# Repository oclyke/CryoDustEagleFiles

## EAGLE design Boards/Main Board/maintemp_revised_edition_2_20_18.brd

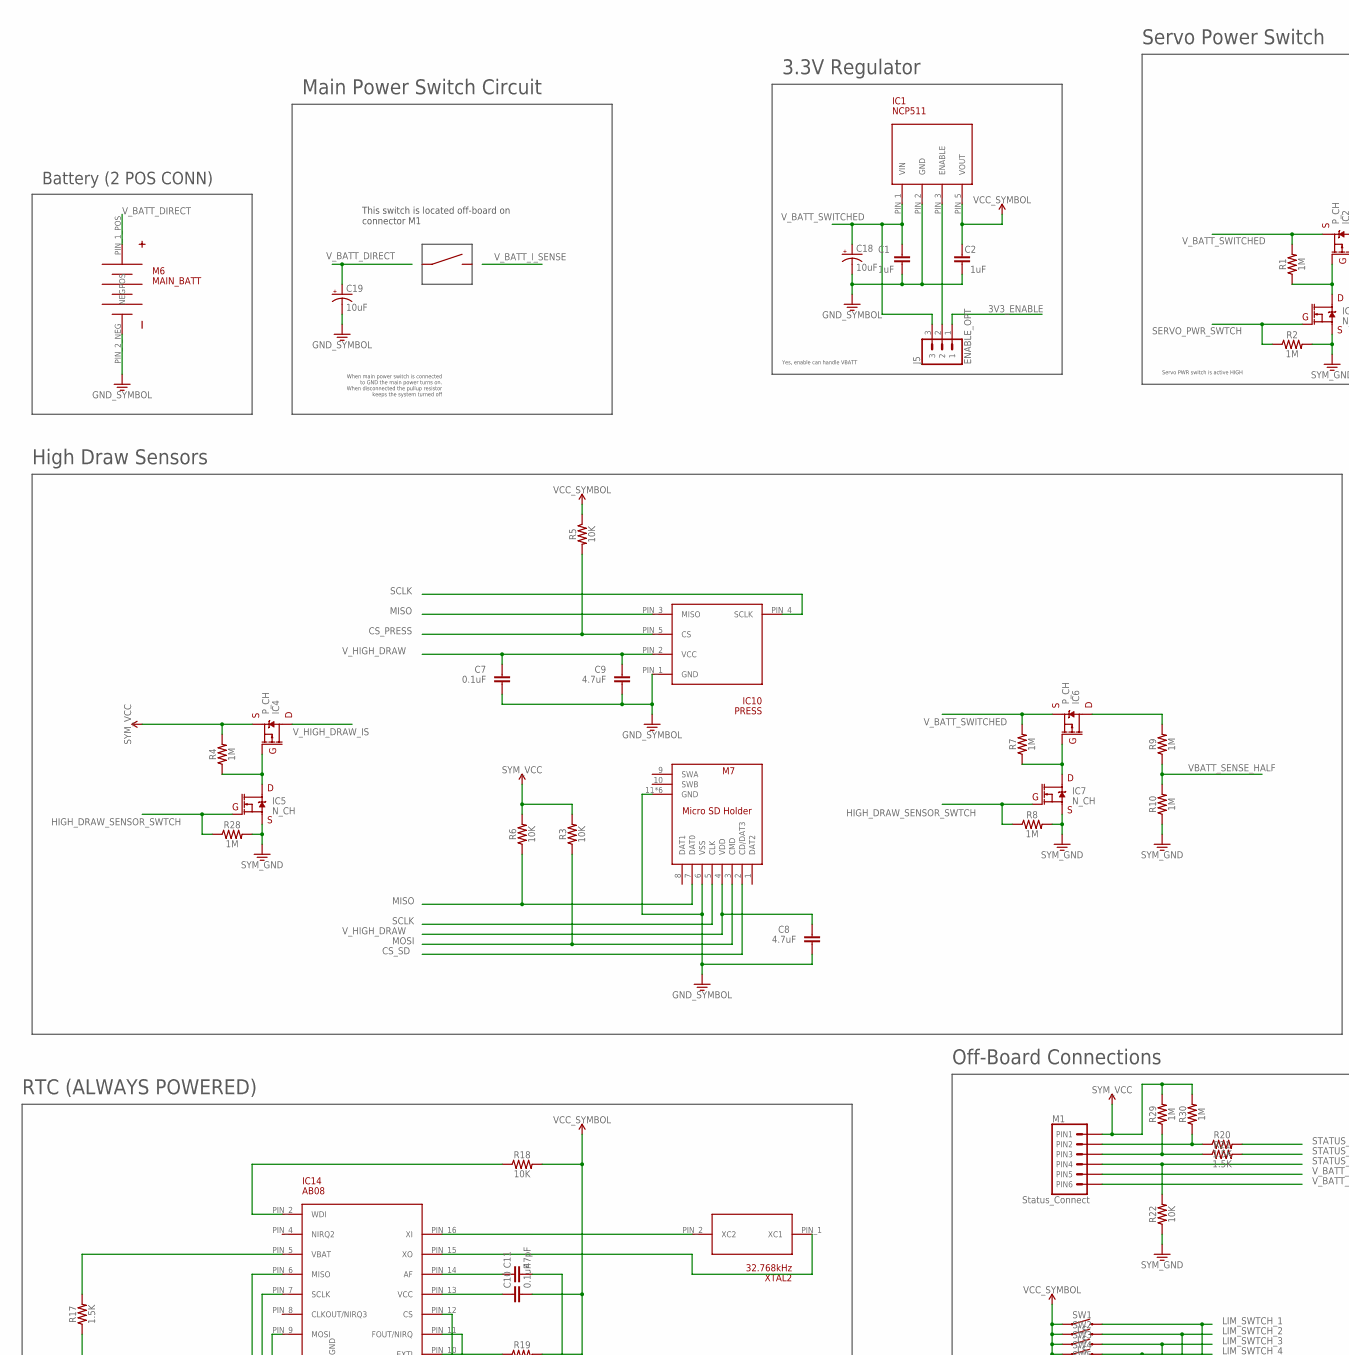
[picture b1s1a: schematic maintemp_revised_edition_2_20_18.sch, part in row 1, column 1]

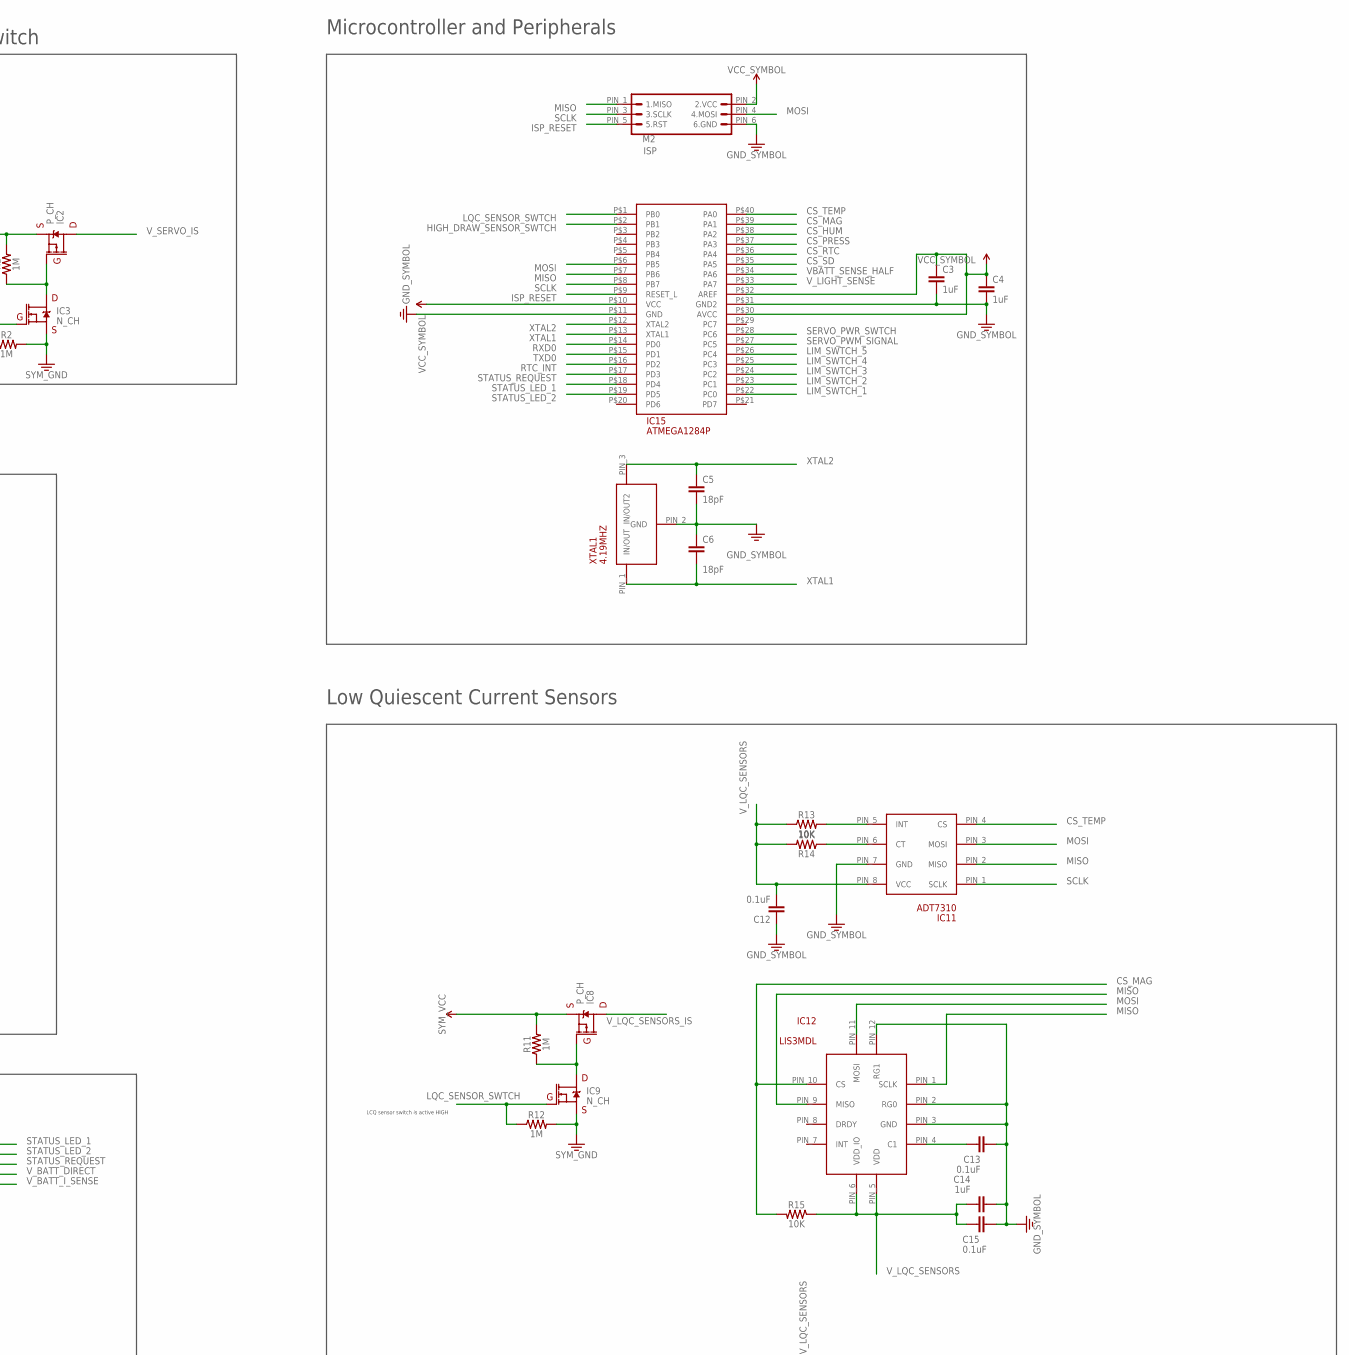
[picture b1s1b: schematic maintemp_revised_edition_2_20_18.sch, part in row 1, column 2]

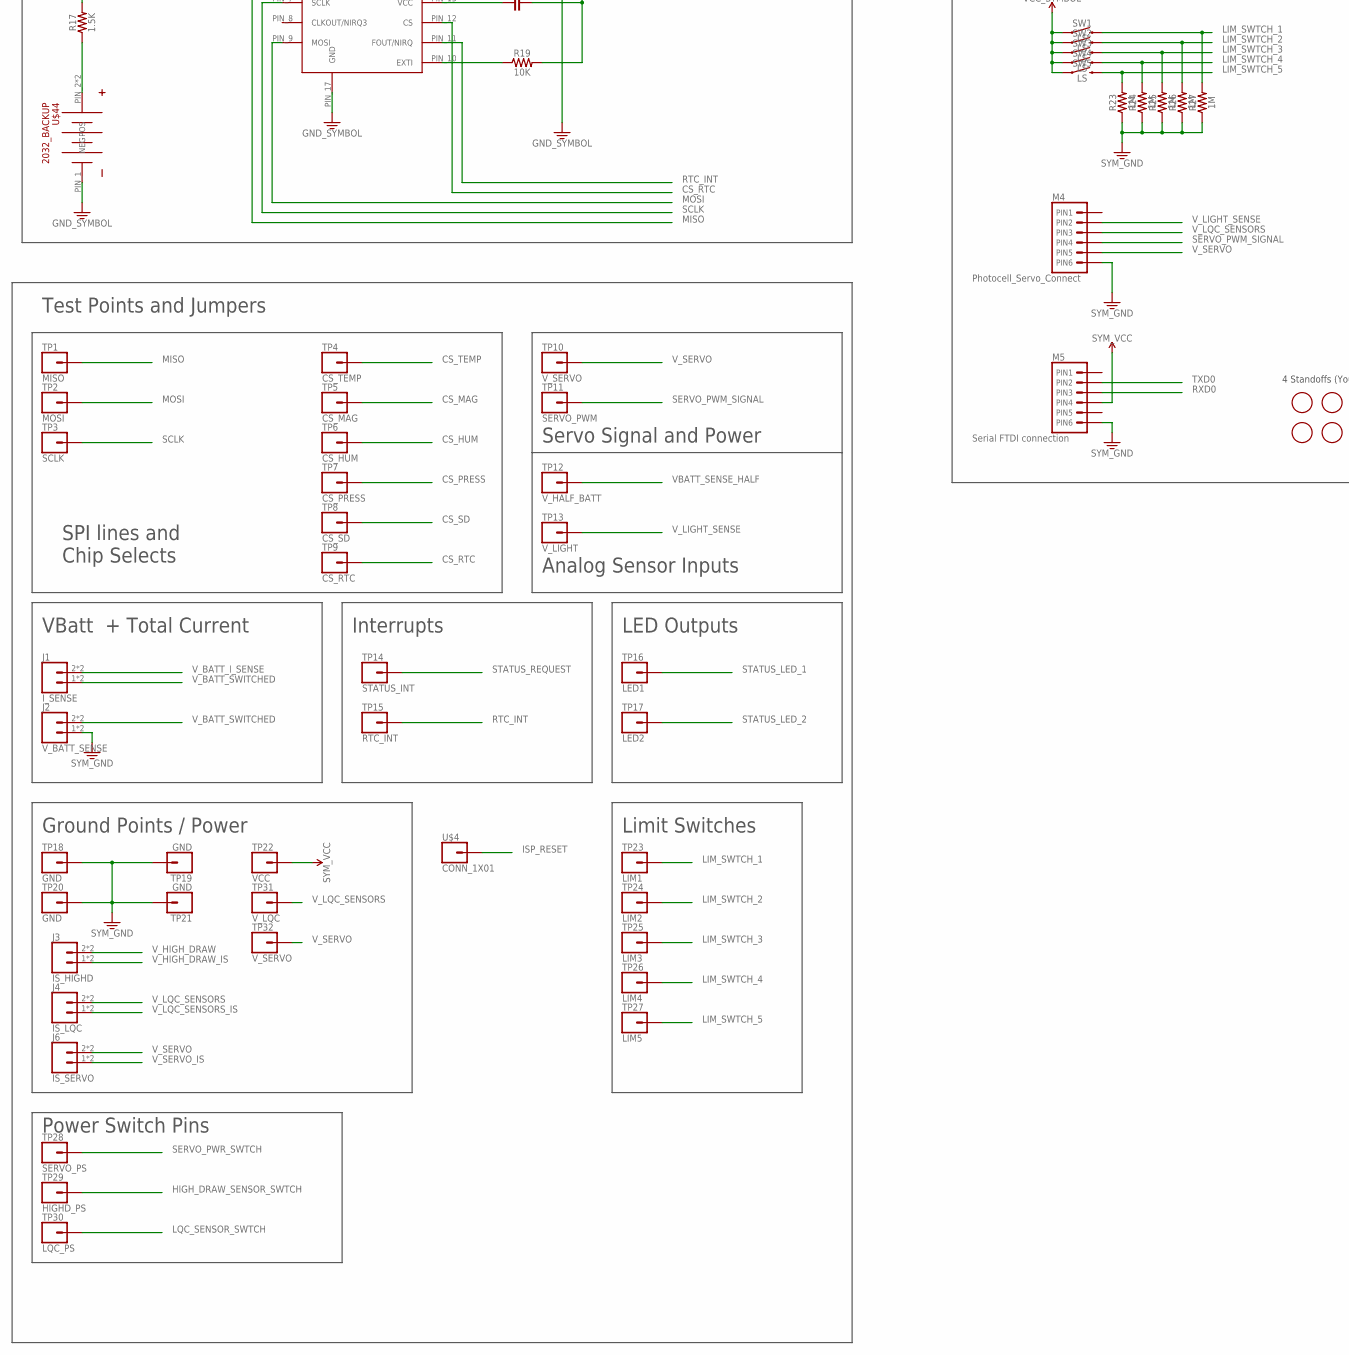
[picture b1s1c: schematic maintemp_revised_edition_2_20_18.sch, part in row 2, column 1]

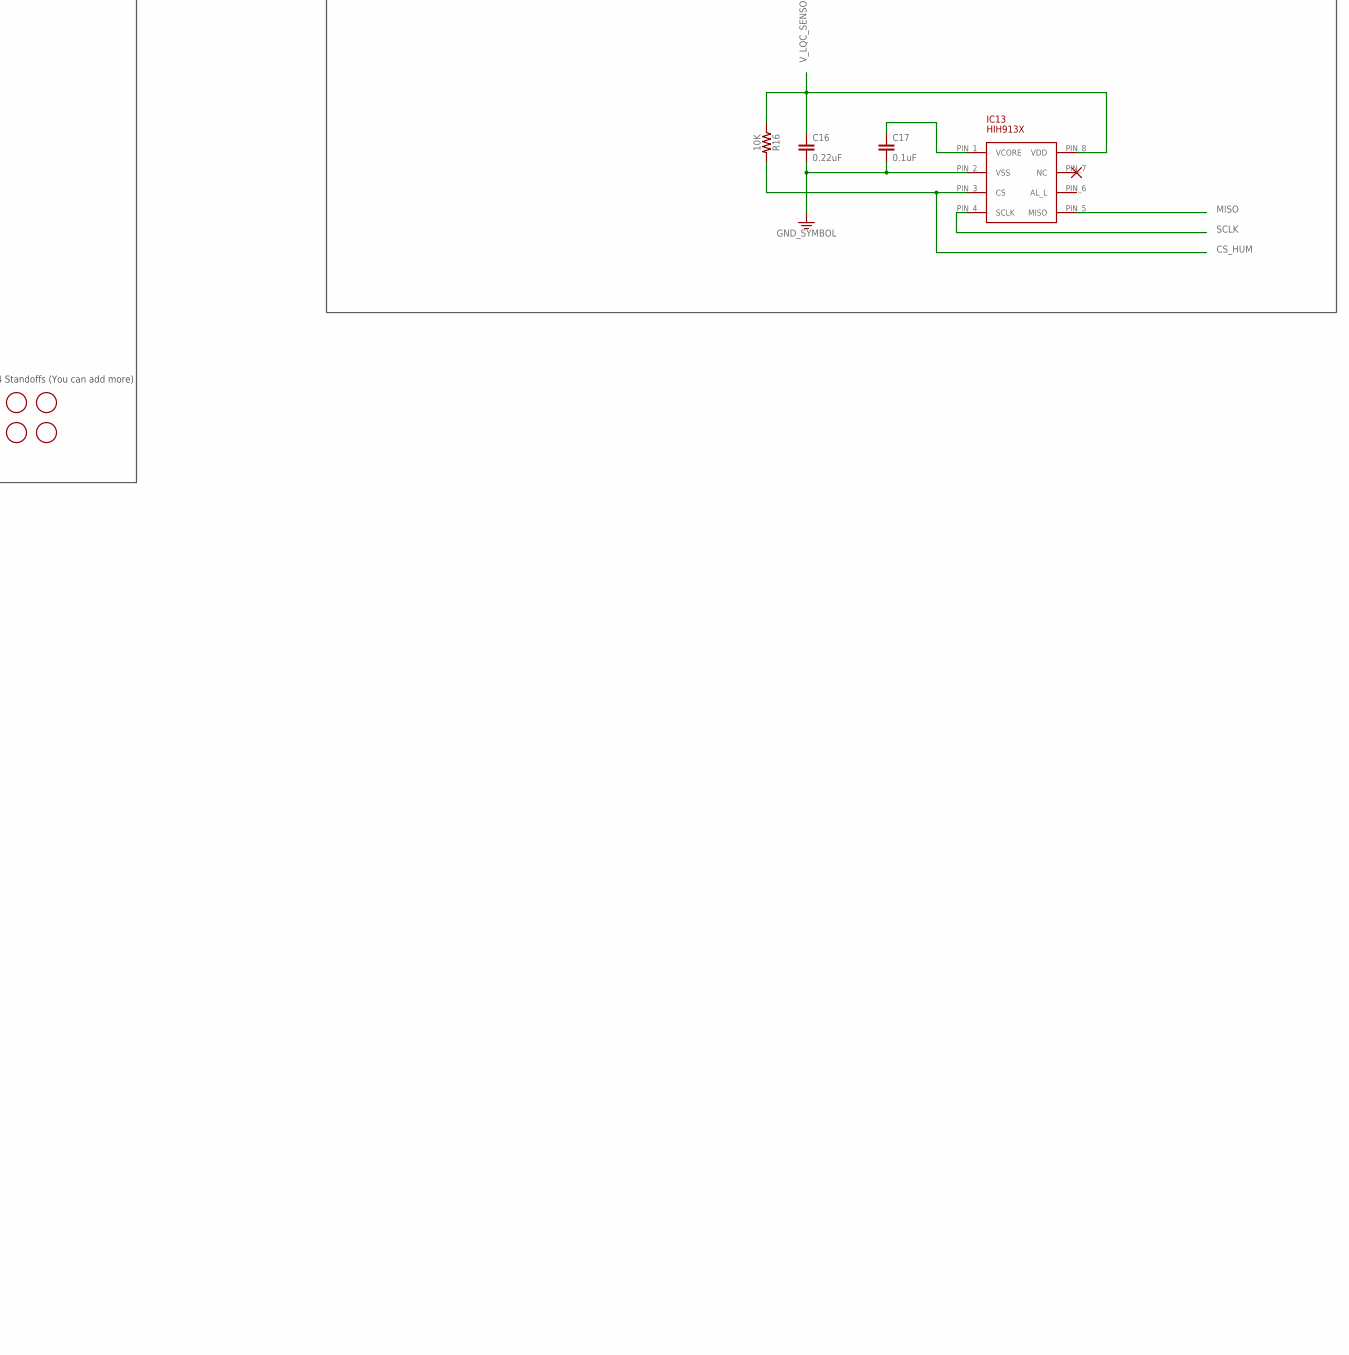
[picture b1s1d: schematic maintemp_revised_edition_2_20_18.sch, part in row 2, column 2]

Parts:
C1, C2, C3, C4, C14: 1uF; SMD_0603
C5, C6: 18pF; SMD_0603
C7, C12, C13, C15, C17: 0.1uF; SMD_0603
C8, C9: 4.7uF; SMD_0603
C10: 0.1uF; 0603
C11: 47pF; 0603
C16: 0.22uF; SMD_0603
C18, C19: 10uF; CAP-PTH-2.54
IC1: NCP511; TSOP-5
IC2, IC4, IC6, IC8: P_CH; SOT23
IC3, IC5, IC7, IC9: N_CH; SOT23
IC10: PRESS; 8-DIP
IC11: ADT7310; SOIC-8
IC12: LIS3MDL; LGA-12
IC13: HIH913X; SOIC-8
IC14: AB08; QFN16_3X3
IC15: ATMEGA1284P; 40-DIP
J1: I_SENSE; 1X02
J2: V_BATT_SENSE; 1X02
J3: IS_HIGHD; 1X02
J4: IS_LQC; 1X02
J5: ENABLE_OPT; 1X03
J6: IS_SERVO; 1X02
M1: Status_Connect; 1X06
M2: ISP; 2X3
M4: Photocell_Servo_Connect; 1X06
M5: Serial FTDI connection; 1X06
M6: MAIN_BATT; 1-1318300-2
M7: SD; MICRO-SD
R1, R2, R4, R7, R8, R9, R10, R11, R12, R23, R24, R25, R26, R27, R28, R29, R30: 1M; SMD_0603
R3, R5, R6, R13, R14, R15, R16, R22: 10K; SMD_0603
R17: 1.5K; 0603
R18, R19: 10K; 0603
R20, R21: 1.5K; SMD_0603
SW1, SW2, SW3, SW4, SW5: LS; SNAPSWITCH
TP1: MISO; 1X01
TP2: MOSI; 1X01
TP3: SCLK; 1X01
TP4: CS_TEMP; 1X01
TP5: CS_MAG; 1X01
TP6: CS_HUM; 1X01
TP7: CS_PRESS; 1X01
TP8: CS_SD; 1X01
TP9: CS_RTC; 1X01
TP10, TP32: V_SERVO; 1X01
TP11: SERVO_PWM; 1X01
TP12: V_HALF_BATT; 1X01
TP13: V_LIGHT; 1X01
TP14: STATUS_INT; 1X01
TP15: RTC_INT; 1X01
TP16: LED1; 1X01
TP17: LED2; 1X01
TP18, TP19, TP20, TP21: GND; 1X01
TP22: VCC; 1X01
TP23: LIM1; 1X01
TP24: LIM2; 1X01
TP25: LIM3; 1X01
TP26: LIM4; 1X01
TP27: LIM5; 1X01
TP28: SERVO_PS; 1X01
TP29: HIGHD_PS; 1X01
TP30: LQC_PS; 1X01
TP31: V_LQC; 1X01
U$4: CONN_1X01; 1X01
U$7, U$11, U$13, U$17: STANDOFF
U$44: 2032_BACKUP; 2032
XTAL1: 4.19MHZ; AT49
XTAL2: 32.768kHz; ABS07

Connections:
3V3_ENABLE: J5.1
CS_HUM: IC13.PIN_3 (CS), IC15.P$38 (PA2), R16.P$2 (2), TP6.1
CS_MAG: IC12.PIN_10 (CS), IC15.P$39 (PA1), R15.P$2 (2), TP5.1
CS_PRESS: IC10.PIN_5 (CS), IC15.P$37 (PA3), R5.P$2 (2), TP7.1
CS_RTC: IC14.PIN_12 (CS), IC15.P$36 (PA4), TP9.1
CS_SD: IC15.P$35 (PA5), M7.2 (CD/DAT3), TP8.1
CS_TEMP: IC11.PIN_4 (CS), IC15.P$40 (PA0), TP4.1
GND: C1.P$2 (2), C2.P$1 (1), C3.P$2 (2), C4.P$2 (2), C5.P$2 (2), C6.P$1 (1), C7.P$2 (2), C8.P$1 (1), C9.P$2 (2), C11.2, C12.P$1 (1), C13.P$1 (1), C14.P$1 (1), C15.P$2 (2), C16.P$2 (2), C17.P$2 (2), C18.2 (-), C19.2 (-), IC1.PIN_2 (GND), IC3.2 (S), IC5.2 (S), IC7.2 (S), IC9.2 (S), IC10.PIN_1 (GND), IC11.PIN_7 (GND), IC12.PIN_2 (RG0), IC12.PIN_3 (GND), IC12.PIN_12 (RG1), IC13.PIN_2 (VSS), IC14.PIN_17 (GND), IC15.P$11 (GND), IC15.P$31 (GND2), J2.1, J2.P$1 (1), M2.PIN_6 (6.GND), M4.1 (PIN6), M5.1 (PIN6), M6.PIN_2_NEG (NEG), M7.6 (VSS), M7.11 (GND), M7.12 (GND), M7.13 (GND), M7.14 (GND), M7.15 (GND), M7.16 (GND), R2.P$2 (2), R8.P$2 (2), R10.P$1 (1), R12.P$2 (2), R22.P$1 (1), R23.P$1 (1), R24.P$1 (1), R25.P$1 (1), R26.P$1 (1), R27.P$1 (1), R28.P$2 (2), TP18.1, TP19.1, TP20.1, TP21.1, U$44.PIN_1 (NEG), XTAL1.PIN_2 (GND)
HIGH_DRAW_SENSOR_SWTCH: IC5.1 (G), IC7.1 (G), IC15.P$2 (PB1), R8.P$1 (1), R28.P$1 (1), TP29.1
ISP_RESET: IC15.P$9 (RESET_L), M2.PIN_5 (5.RST), U$4.1
LIM_SWTCH_1: IC15.P$22 (PC0), R27.P$2 (2), SW1.PIN_2 (2), TP23.1
LIM_SWTCH_2: IC15.P$23 (PC1), R26.P$2 (2), SW2.PIN_2 (2), TP24.1
LIM_SWTCH_3: IC15.P$24 (PC2), R25.P$2 (2), SW3.PIN_2 (2), TP25.1
LIM_SWTCH_4: IC15.P$25 (PC3), R24.P$2 (2), SW4.PIN_2 (2), TP26.1
LIM_SWTCH_5: IC15.P$26 (PC4), R23.P$2 (2), SW5.PIN_2 (2), TP27.1
LQC_SENSOR_SWTCH: IC9.1 (G), IC15.P$1 (PB0), R12.P$1 (1), TP30.1
MISO: IC10.PIN_3 (MISO), IC11.PIN_2 (MISO), IC12.PIN_1 (SCLK), IC12.PIN_9 (MISO), IC13.PIN_5 (MISO), IC14.PIN_6 (MISO), IC15.P$7 (PB6), M2.PIN_1 (1.MISO), M7.7 (DAT0), R6.P$1 (1), TP1.1
MOSI: IC11.PIN_3 (MOSI), IC12.PIN_11 (MOSI), IC14.PIN_9 (MOSI), IC15.P$6 (PB5), M2.PIN_4 (4.MOSI), M7.3 (CMD), R3.P$1 (1), TP2.1
unnamed: IC2.1 (G), IC3.3 (D), R1.P$1 (1)
unnamed: C17.P$1 (1), IC13.PIN_1 (VCORE)
unnamed: C13.P$2 (2), IC12.PIN_4 (C1)
unnamed: IC14.PIN_2 (WDI), R18.1
unnamed: IC14.PIN_10 (EXTI), R19.1
unnamed: C10.1, IC14.PIN_13 (VCC)
unnamed: C11.1, IC14.PIN_14 (AF)
unnamed: IC14.PIN_15 (XO), XTAL2.PIN_1 (XC1)
unnamed: IC14.PIN_16 (XI), XTAL2.PIN_2 (XC2)
unnamed: R17.1, U$44.PIN_2 (POS), U$44.PIN_3 (POS)
unnamed: IC14.PIN_5 (VBAT), R17.2
unnamed: IC11.PIN_5 (INT), R13.P$2 (2)
unnamed: IC11.PIN_6 (CT), R14.P$1 (1)
unnamed: IC1.PIN_3 (ENABLE), J5.2
unnamed: IC6.1 (G), IC7.3 (D), R7.P$1 (1)
unnamed: IC4.1 (G), IC5.3 (D), R4.P$1 (1)
unnamed: IC8.1 (G), IC9.3 (D), R11.P$1 (1)
N$L1: M1.5 (PIN2), R20.P$1 (1), R30.P$1 (1)
N$L2: M1.4 (PIN3), R21.P$1 (1), R29.P$1 (1)
RTC_INT: IC14.PIN_11 (FOUT/NIRQ), IC15.P$16 (PD2), TP15.1
RXD0: IC15.P$14 (PD0), M5.4 (PIN3)
SCLK: IC10.PIN_4 (SCLK), IC11.PIN_1 (SCLK), IC13.PIN_4 (SCLK), IC14.PIN_7 (SCLK), IC15.P$8 (PB7), M2.PIN_3 (3.SCLK), M7.5 (CLK), TP3.1
SERVO_PWM_SIGNAL: IC15.P$27 (PC5), M4.3 (PIN4), TP11.1
SERVO_PWR_SWTCH: IC3.1 (G), IC15.P$28 (PC6), R2.P$1 (1), TP28.1
STATUS_LED_1: IC15.P$18 (PD4), R20.P$2 (2), TP16.1
STATUS_LED_2: IC15.P$19 (PD5), R21.P$2 (2), TP17.1
STATUS_REQUEST: IC15.P$17 (PD3), M1.3 (PIN4), R22.P$2 (2), TP14.1
TXD0: IC15.P$15 (PD1), M5.5 (PIN2)
VBATT_SENSE_HALF: IC15.P$34 (PA6), R9.P$1 (1), R10.P$2 (2), TP12.1
VCC: C2.P$2 (2), C3.P$1 (1), C4.P$1 (1), C10.2, IC1.PIN_5 (VOUT), IC4.2 (S), IC8.2 (S), IC15.P$10 (VCC), IC15.P$30 (AVCC), IC15.P$32 (AREF), M1.6 (PIN1), M2.PIN_2 (2.VCC), M5.3 (PIN4), R3.P$2 (2), R4.P$2 (2), R5.P$1 (1), R6.P$2 (2), R11.P$2 (2), R18.2, R19.2, R29.P$2 (2), R30.P$2 (2), SW1.PIN_1 (1), SW2.PIN_1 (1), SW3.PIN_1 (1), SW4.PIN_1 (1), SW5.PIN_1 (1), TP22.1
V_BATT_DIRECT: C19.1 (+), M1.2 (PIN5), M6.PIN_1_POS (POS)
V_BATT_I_SENSE: J1.2, J1.P$2 (2), M1.1 (PIN6)
V_BATT_SENSE_WHOLE: IC6.3 (D), R9.P$2 (2)
V_BATT_SWITCHED: C1.P$1 (1), C18.1 (+), IC1.PIN_1 (VIN), IC2.2 (S), IC6.2 (S), J1.1, J1.P$1 (1), J2.2, J2.P$2 (2), J5.3, R1.P$2 (2), R7.P$2 (2)
V_HIGH_DRAW: C7.P$1 (1), C8.P$2 (2), C9.P$1 (1), IC10.PIN_2 (VCC), J3.2, J3.P$2 (2), M7.4 (VDD)
V_HIGH_DRAW_IS: IC4.3 (D), J3.1, J3.P$1 (1)
V_LIGHT_SENSE: IC15.P$33 (PA7), M4.5 (PIN2), TP13.1
V_LQC_SENSORS: C12.P$2 (2), C14.P$2 (2), C15.P$1 (1), C16.P$1 (1), IC11.PIN_8 (VCC), IC12.PIN_5 (VDD), IC12.PIN_6 (VDD_IO), IC13.PIN_8 (VDD), J4.2, J4.P$2 (2), M4.4 (PIN3), R13.P$1 (1), R14.P$2 (2), R15.P$1 (1), R16.P$1 (1), TP31.1
V_LQC_SENSORS_IS: IC8.3 (D), J4.1, J4.P$1 (1)
V_SERVO: J6.2, J6.P$2 (2), M4.2 (PIN5), TP10.1, TP32.1
V_SERVO_IS: IC2.3 (D), J6.1, J6.P$1 (1)
XTAL1: C6.P$2 (2), IC15.P$13 (XTAL1), XTAL1.PIN_1 (IN/OUT)
XTAL2: C5.P$1 (1), IC15.P$12 (XTAL2), XTAL1.PIN_3 (IN/OUT2)

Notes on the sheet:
Battery (2 POS CONN)
3.3V Regulator
Main Power Switch Circuit
High Draw Sensors
Low Quiescent Current Sensors
RTC (ALWAYS POWERED)
Microcontroller and Peripherals
Off-Board Connections
Servo Power Switch
When main power switch is connected to GND the main power turns on. When disconnected the pullup resistor keeps the system turned off
Yes, enable can handle VBATT
Servo PWR switch is active HIGH
LCQ sensor switch is active HIGH
This switch is located off-board on connector M1
Test Points and Jumpers
SPI lines and Chip Selects
VBatt + Total Current
Servo Signal and Power
Analog Sensor Inputs
Interrupts
Ground Points / Power
LED Outputs
Power Switch Pins
Limit Switches
4 Standoffs (You can add more)

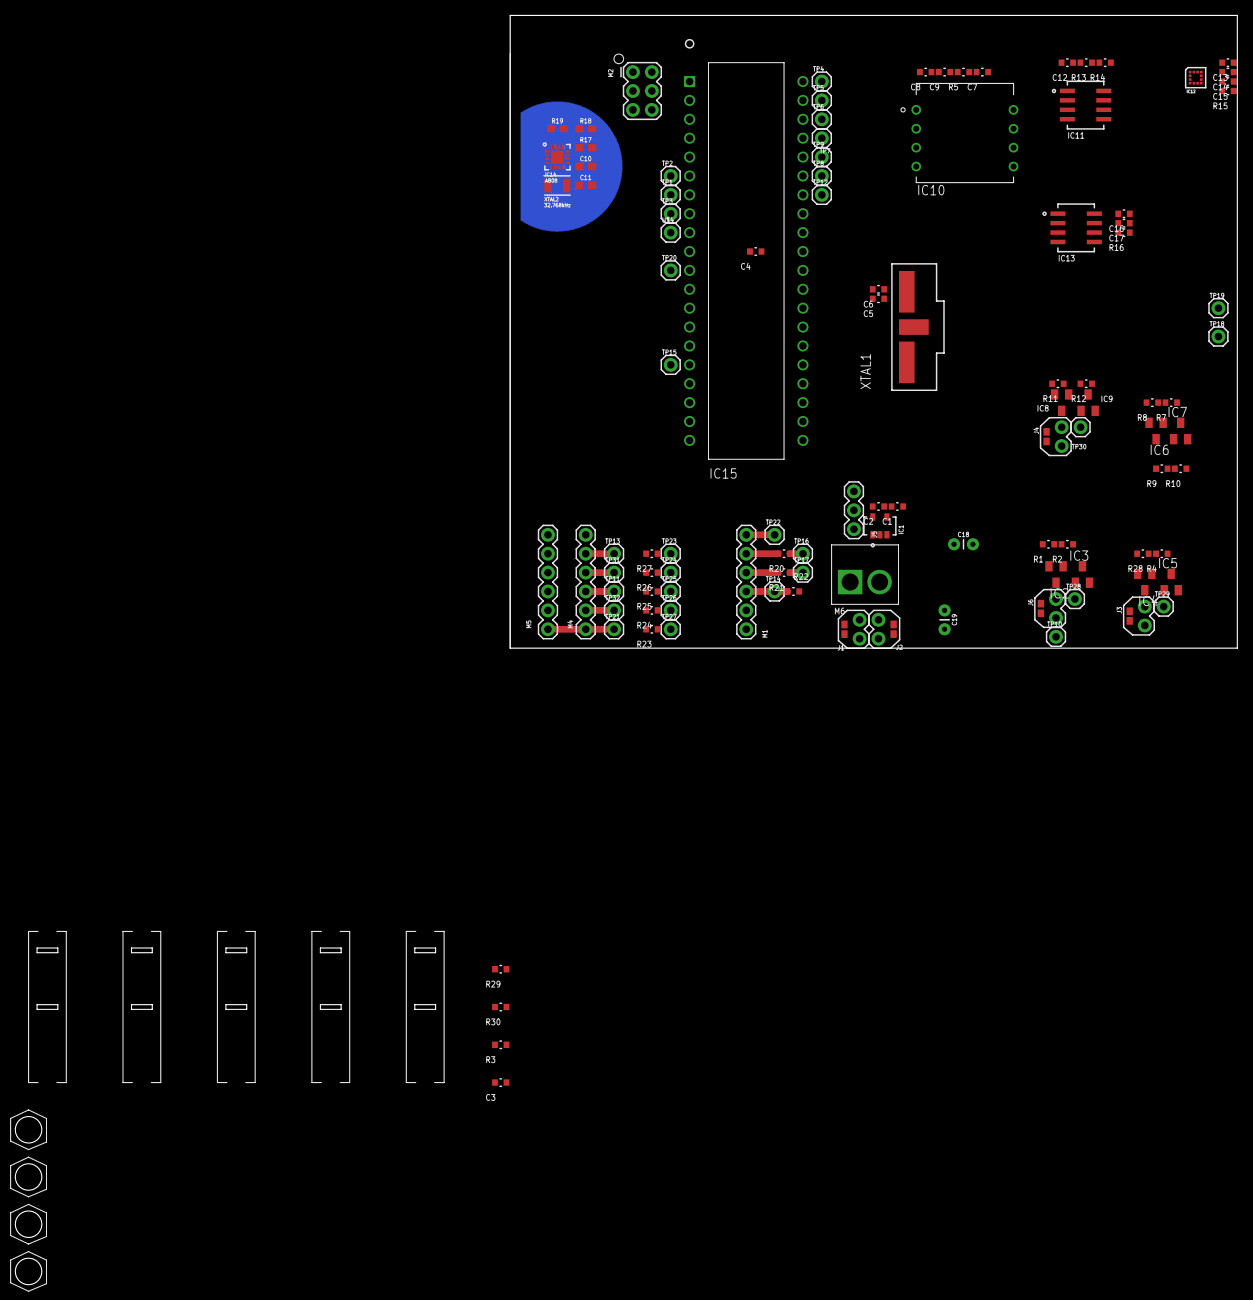
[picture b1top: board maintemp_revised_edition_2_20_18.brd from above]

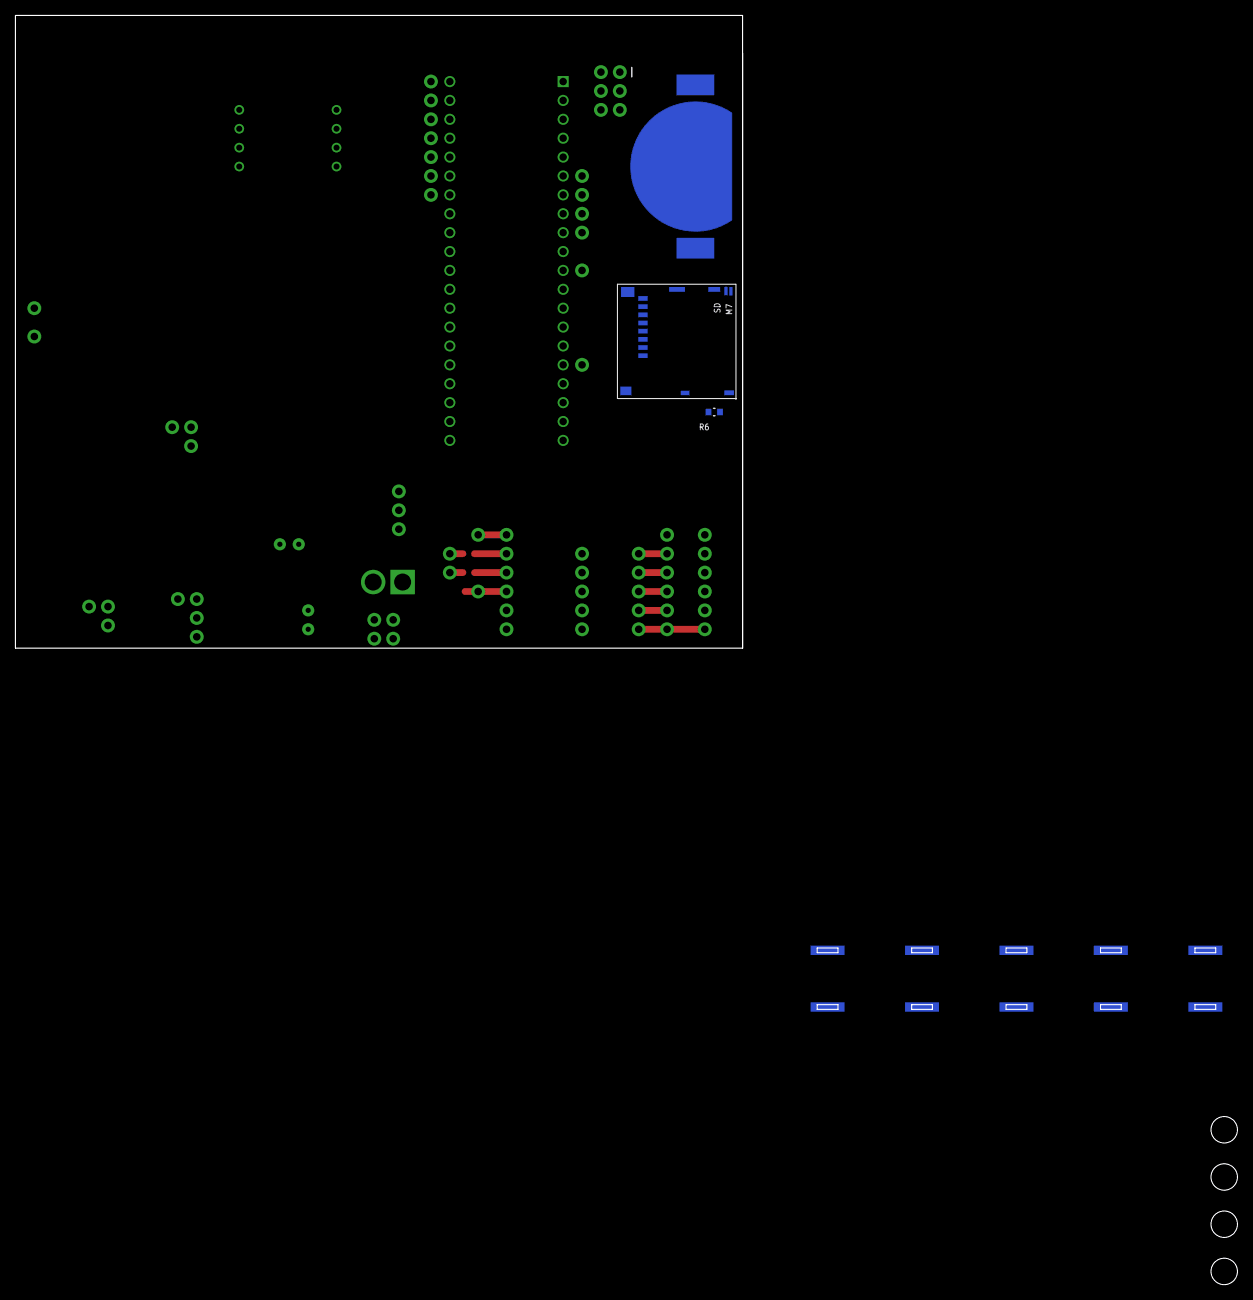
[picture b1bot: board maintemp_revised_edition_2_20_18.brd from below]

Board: 2 copper layers, 164.3 x 170.7 mm, 121 parts (3 on the bottom side), 60 nets.

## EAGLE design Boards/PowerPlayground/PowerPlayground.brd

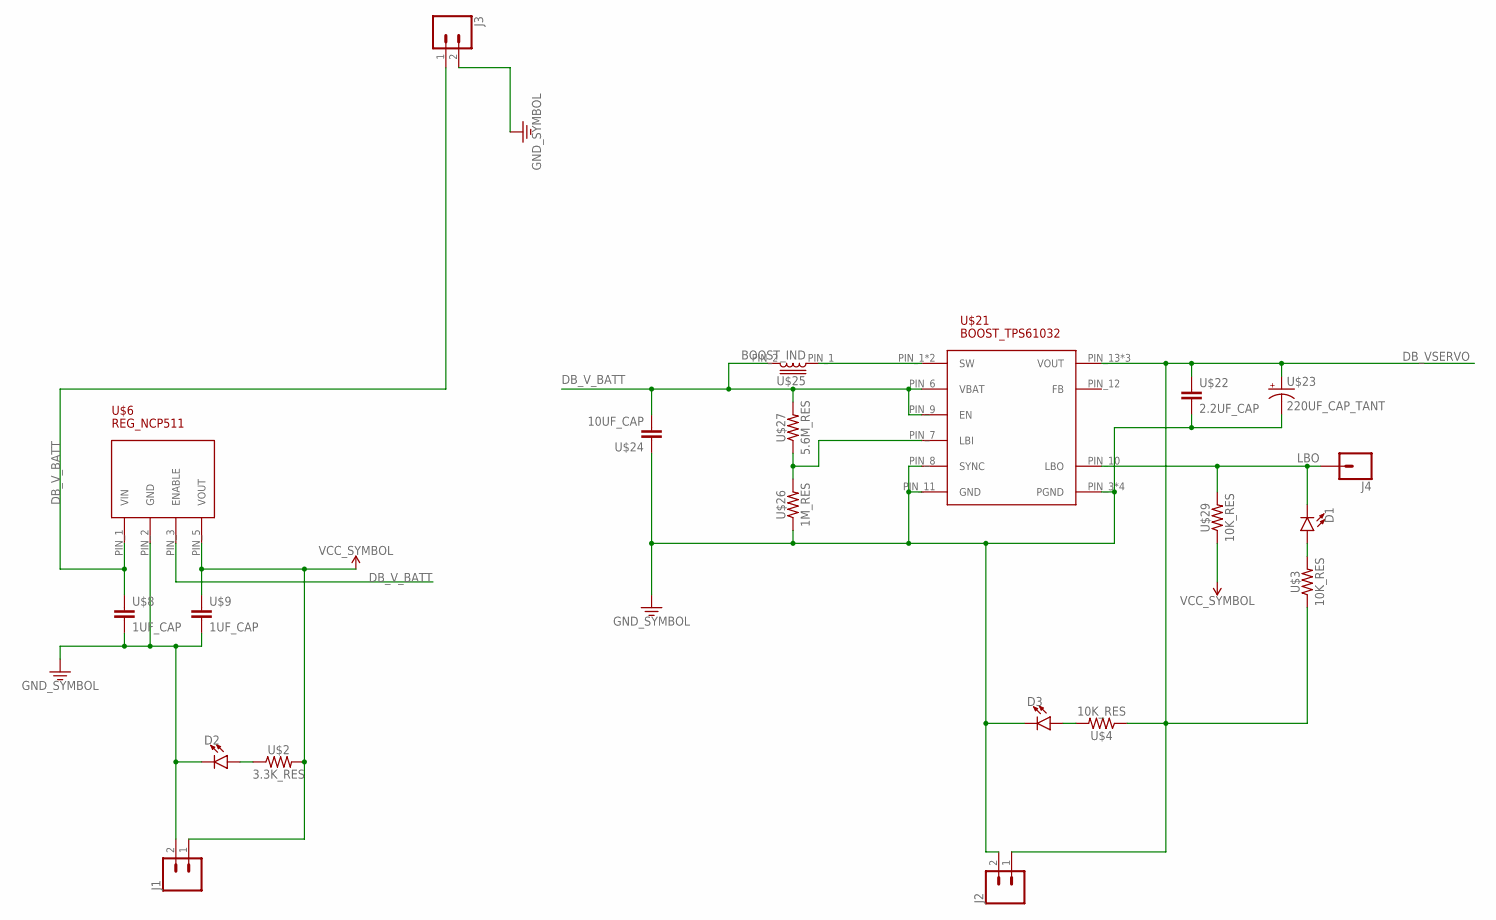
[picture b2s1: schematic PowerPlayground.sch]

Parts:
D1, D2, D3: LED5MM; LED_5MM
J1, J2, J3: CONN_02PTH3; 1X02_LONGPADS
J4: CONN_01OFFSET; 1X01_OFFSET
U$2: 3.3K_RES; 0603
U$3, U$4, U$29: 10K_RES; 0603
U$6: REG_NCP511; TSOP-5
U$8, U$9: 1UF_CAP; 0603
U$21: BOOST_TPS61032; PWP-16
U$22: 2.2UF_CAP; 0603
U$23: 220UF_CAP_TANT; 7343
U$24: 10UF_CAP; 0603
U$25: BOOST_IND; VLS6045EX
U$26: 1M_RES; 0603
U$27: 5.6M_RES; 0603

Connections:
DB_VSERVO: J2.1, U$3.1, U$4.1, U$21.PIN_13 (VOUT), U$21.PIN_14 (VOUT), U$21.PIN_15 (VOUT), U$22.1, U$23.PIN_2_+ (+)
DB_V_BATT: J3.1, U$6.PIN_1 (VIN), U$6.PIN_3 (ENABLE), U$8.1, U$21.PIN_6 (VBAT), U$21.PIN_9 (EN), U$24.2, U$25.PIN_2, U$27.2
GND: D2.K (C), D3.K (C), J1.2, J2.2, J3.2, U$6.PIN_2 (GND), U$8.2, U$9.2, U$21.PIN_3 (PGND), U$21.PIN_4 (PGND), U$21.PIN_5 (PGND), U$21.PIN_8 (SYNC), U$21.PIN_11 (GND), U$21.PIN_17 (PGND), U$22.2, U$23.PIN_1_- (-), U$24.1, U$26.1
LBO: D1.K (C), J4.1, U$21.PIN_10 (LBO), U$29.2
unnamed: D2.A, U$2.1
unnamed: U$21.PIN_7 (LBI), U$26.2, U$27.1
unnamed: U$21.PIN_1 (SW), U$21.PIN_2 (SW), U$25.PIN_1
unnamed: D3.A, U$4.2
unnamed: D1.A, U$3.2
VCC: J1.1, U$2.2, U$6.PIN_5 (VOUT), U$9.1, U$29.1

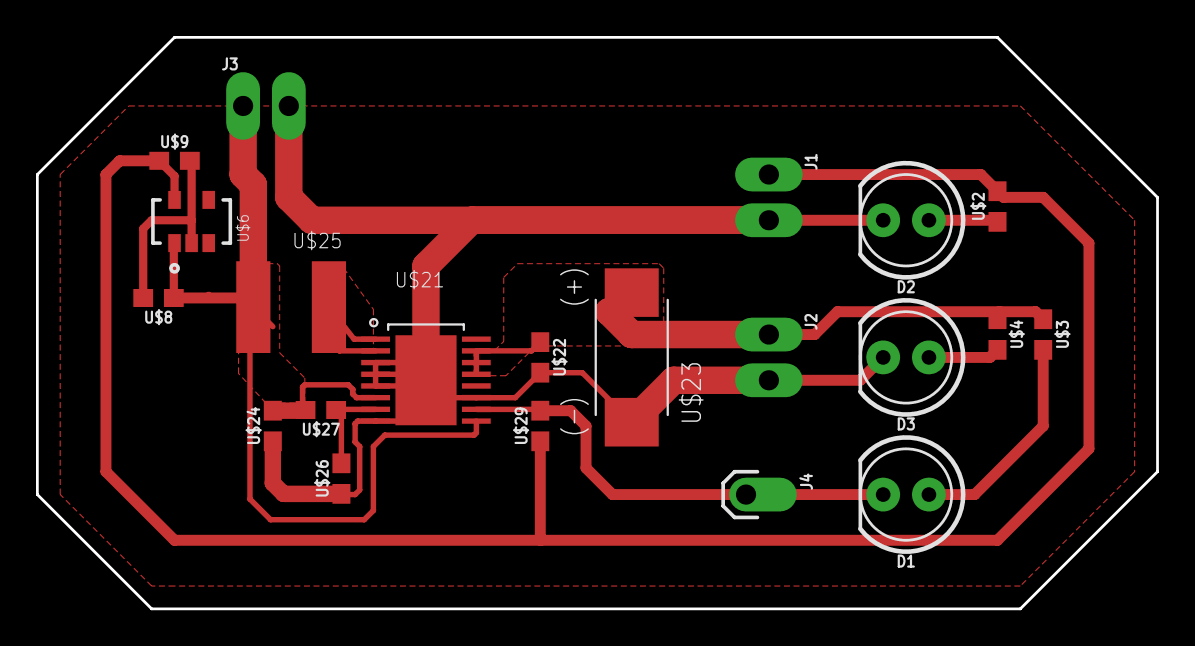
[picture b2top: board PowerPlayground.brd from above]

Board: 2 copper layers, 62.2 x 31.8 mm, 21 parts (0 on the bottom side), 10 nets.

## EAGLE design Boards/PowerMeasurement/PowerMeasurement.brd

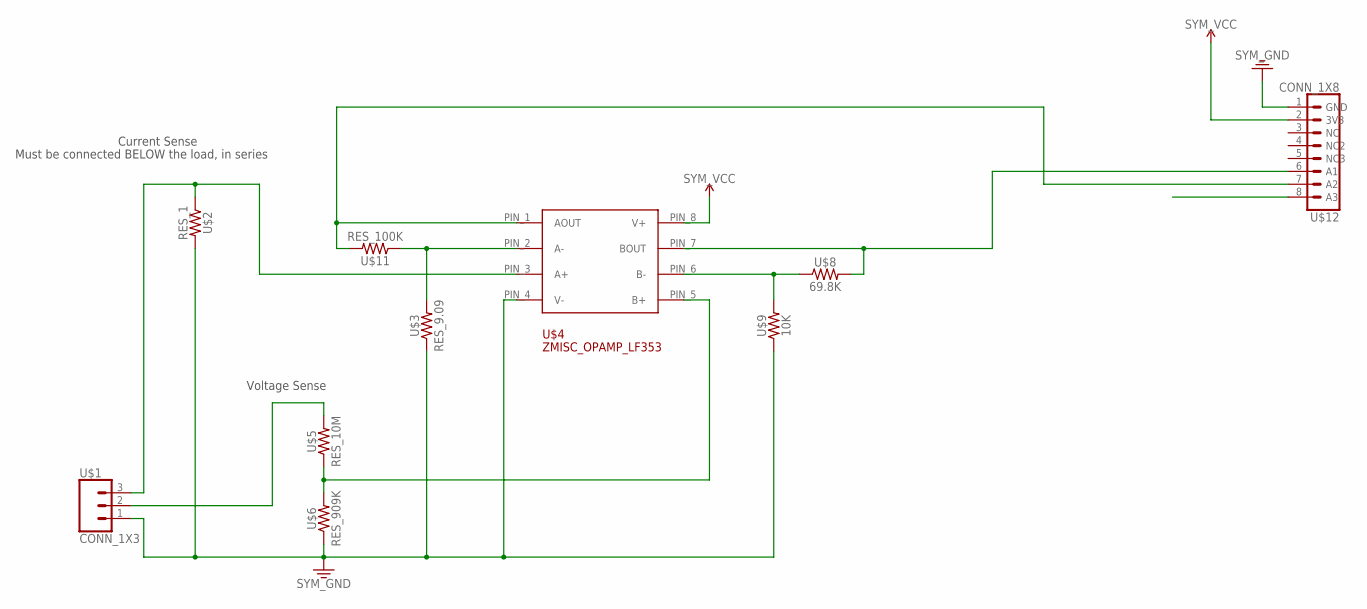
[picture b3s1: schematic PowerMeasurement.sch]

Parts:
U$1: CONN_1X3; 1X03
U$2: RES_1; SMD_2512
U$3: RES_9.09; SMD_0603
U$4: ZMISC_OPAMP_LF353; SOIC-8
U$5: RES_10M; SMD_1206
U$6: RES_909K; SMD_0805
U$8: 69.8K; SMD_0603
U$9: 10K; SMD_0603
U$11: RES_100K; SMD_0603
U$12: CONN_1X8; 1X08_LOCK

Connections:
GND: U$1.1, U$2.P$2 (2), U$3.P$1 (1), U$4.PIN_4 (V-), U$6.P$1 (1), U$9.P$1 (1), U$12.1 (GND)
unnamed: U$1.3, U$2.P$1 (1), U$4.PIN_3 (A+)
unnamed: U$4.PIN_6 (B-), U$8.P$1 (1), U$9.P$2 (2)
unnamed: U$1.2, U$5.P$2 (2)
unnamed: U$4.PIN_5 (B+), U$5.P$1 (1), U$6.P$2 (2)
unnamed: U$3.P$2 (2), U$4.PIN_2 (A-), U$11.P$1 (1)
SCALED_CURRENT_OUT: U$4.PIN_1 (AOUT), U$11.P$2 (2), U$12.7 (A2)
SCALED_VOLTAGE_OUT: U$4.PIN_7 (BOUT), U$8.P$2 (2), U$12.6 (A1)
VCC: U$4.PIN_8 (V+), U$12.2 (3V3)

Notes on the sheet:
Voltage Sense
Current Sense
Must be connected BELOW the load, in series

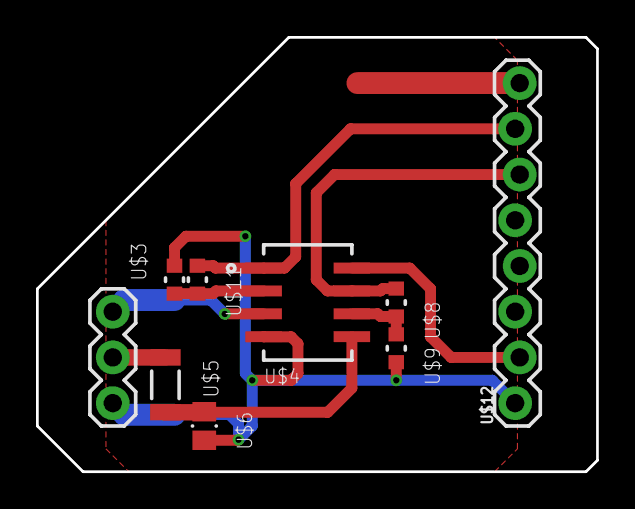
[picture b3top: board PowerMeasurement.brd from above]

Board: 2 copper layers, 31.1 x 24.1 mm, 10 parts (1 on the bottom side), 9 nets.

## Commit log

2018-01-31 Updated the library
2018-02-01 Added a boost converter
2018-02-02 I added new library components, update the boost DBL to use available caps, and made a photodiode amplifier DBL
2018-02-02 I standardized the library device naming convention, and fixed confusion regarding the defference between metric and imperial 0603 packages. All CAP/RES SMD packages are now specified in imperial. Th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
2018-02-03 I cleaned up the design blocks. I tried to use the new packages, but I didnt want to mess with either the boost converter or RTC so they still have the old 0603 package (it seems close enough)
2018-02-06 I am just trying to figure out why my files were gone when I came back. Added .gitignore
2018-02-06 Added CAM file with specific references to this directory. Probably won't work on your machine
2018-02-06 Added SD card from Riley. Updated gitignore
2018-02-06 Added a lot of little connectors to library and added a jumper design block
2018-02-07 In this commit I added a library for the power measurement board, as well as the board and output gerber files.
2018-02-07 Just added a small lip for mechanical relief on the connectors
2018-02-07 Added a ground pour
2018-02-07 I fixed clearance on the lower pour
2018-02-11 I updated the battery connector drill hole size to fit the pins, and I also included a new board called "Package Check" that I used to verify that all the packages were correct.
2018-02-13 Added a 3 pin connector for option jumpers
2018-02-14 Added a mosfet package
2018-02-24 Added standoff part, switches, main board file, and others

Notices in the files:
parts and their libraries:
SparkFun-Connectors: Licensing: Creative Commons ShareAlike 4.0 International - https://creativecommons.org/licenses/by-sa/4.0
